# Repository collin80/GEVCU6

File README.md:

GEVCU
=====

Generalized Electric Vehicle Control Unit

Our website can be found at : http://www.evtv.me

A project to create a fairly Arduino compatible ECU firmware
to interface with various electric vehicle hardware over CANbus
(and possibly other comm channels)

The project now builds in the Arduino IDE. So, use it to compile, send the firmware to the GEVCU hardware, and monitor serial. It all works very nicely.

You will need the following to have any hope of compiling and running the firmware:
- A GEVCU board. This version supports hardware 6.23c and later.
- Arduino IDE 1.5.4 - or later even 1.8.13 or such newer IDEs should work fine.
-All libraries reside in the lib folder

All libraries belong in %USERPROFILE%\Documents\Arduino\libraries (Windows) or ~/Arduino/libraries (Linux/Mac).
You will need to remove -master or any other postfixes. Your library folders should be named as above.

The canbus is supposed to be terminated on both ends of the bus. If you are testing with a DMOC and GEVCU then you've got two devices, each on opposing ends of the bus. GEVCU hardware is already terminated internally.

This software is MIT licensed:

Copyright (c) 2014 Collin Kidder, Michael Neuweiler, Charles Galpin, Jack Rickard

Permission is hereby granted, free of charge, to any person obtaining
a copy of this software and associated documentation files (the
"Software"), to deal in the Software without restriction, including
without limitation the rights to use, copy, modify, merge, publish,
distribute, sublicense, and/or sell copies of the Software, and to
permit persons to whom the Software is furnished to do so, subject to
the following conditions:

The above copyright notice and this permission notice shall be included
in all copies or substantial portions of the Software.

THE SOFTWARE IS PROVIDED "AS IS", WITHOUT WARRANTY OF ANY KIND,
EXPRESS OR IMPLIED, INCLUDING BUT NOT LIMITED TO THE WARRANTIES OF
MERCHANTABILITY, FITNESS FOR A PARTICULAR PURPOSE AND NONINFRINGEMENT.
IN NO EVENT SHALL THE AUTHORS OR COPYRIGHT HOLDERS BE LIABLE FOR ANY
CLAIM, DAMAGES OR OTHER LIABILITY, WHETHER IN AN ACTION OF CONTRACT,
TORT OR OTHERWISE, ARISING FROM, OUT OF OR IN CONNECTION WITH THE
SOFTWARE OR THE USE OR OTHER DEALINGS IN THE SOFTWARE.

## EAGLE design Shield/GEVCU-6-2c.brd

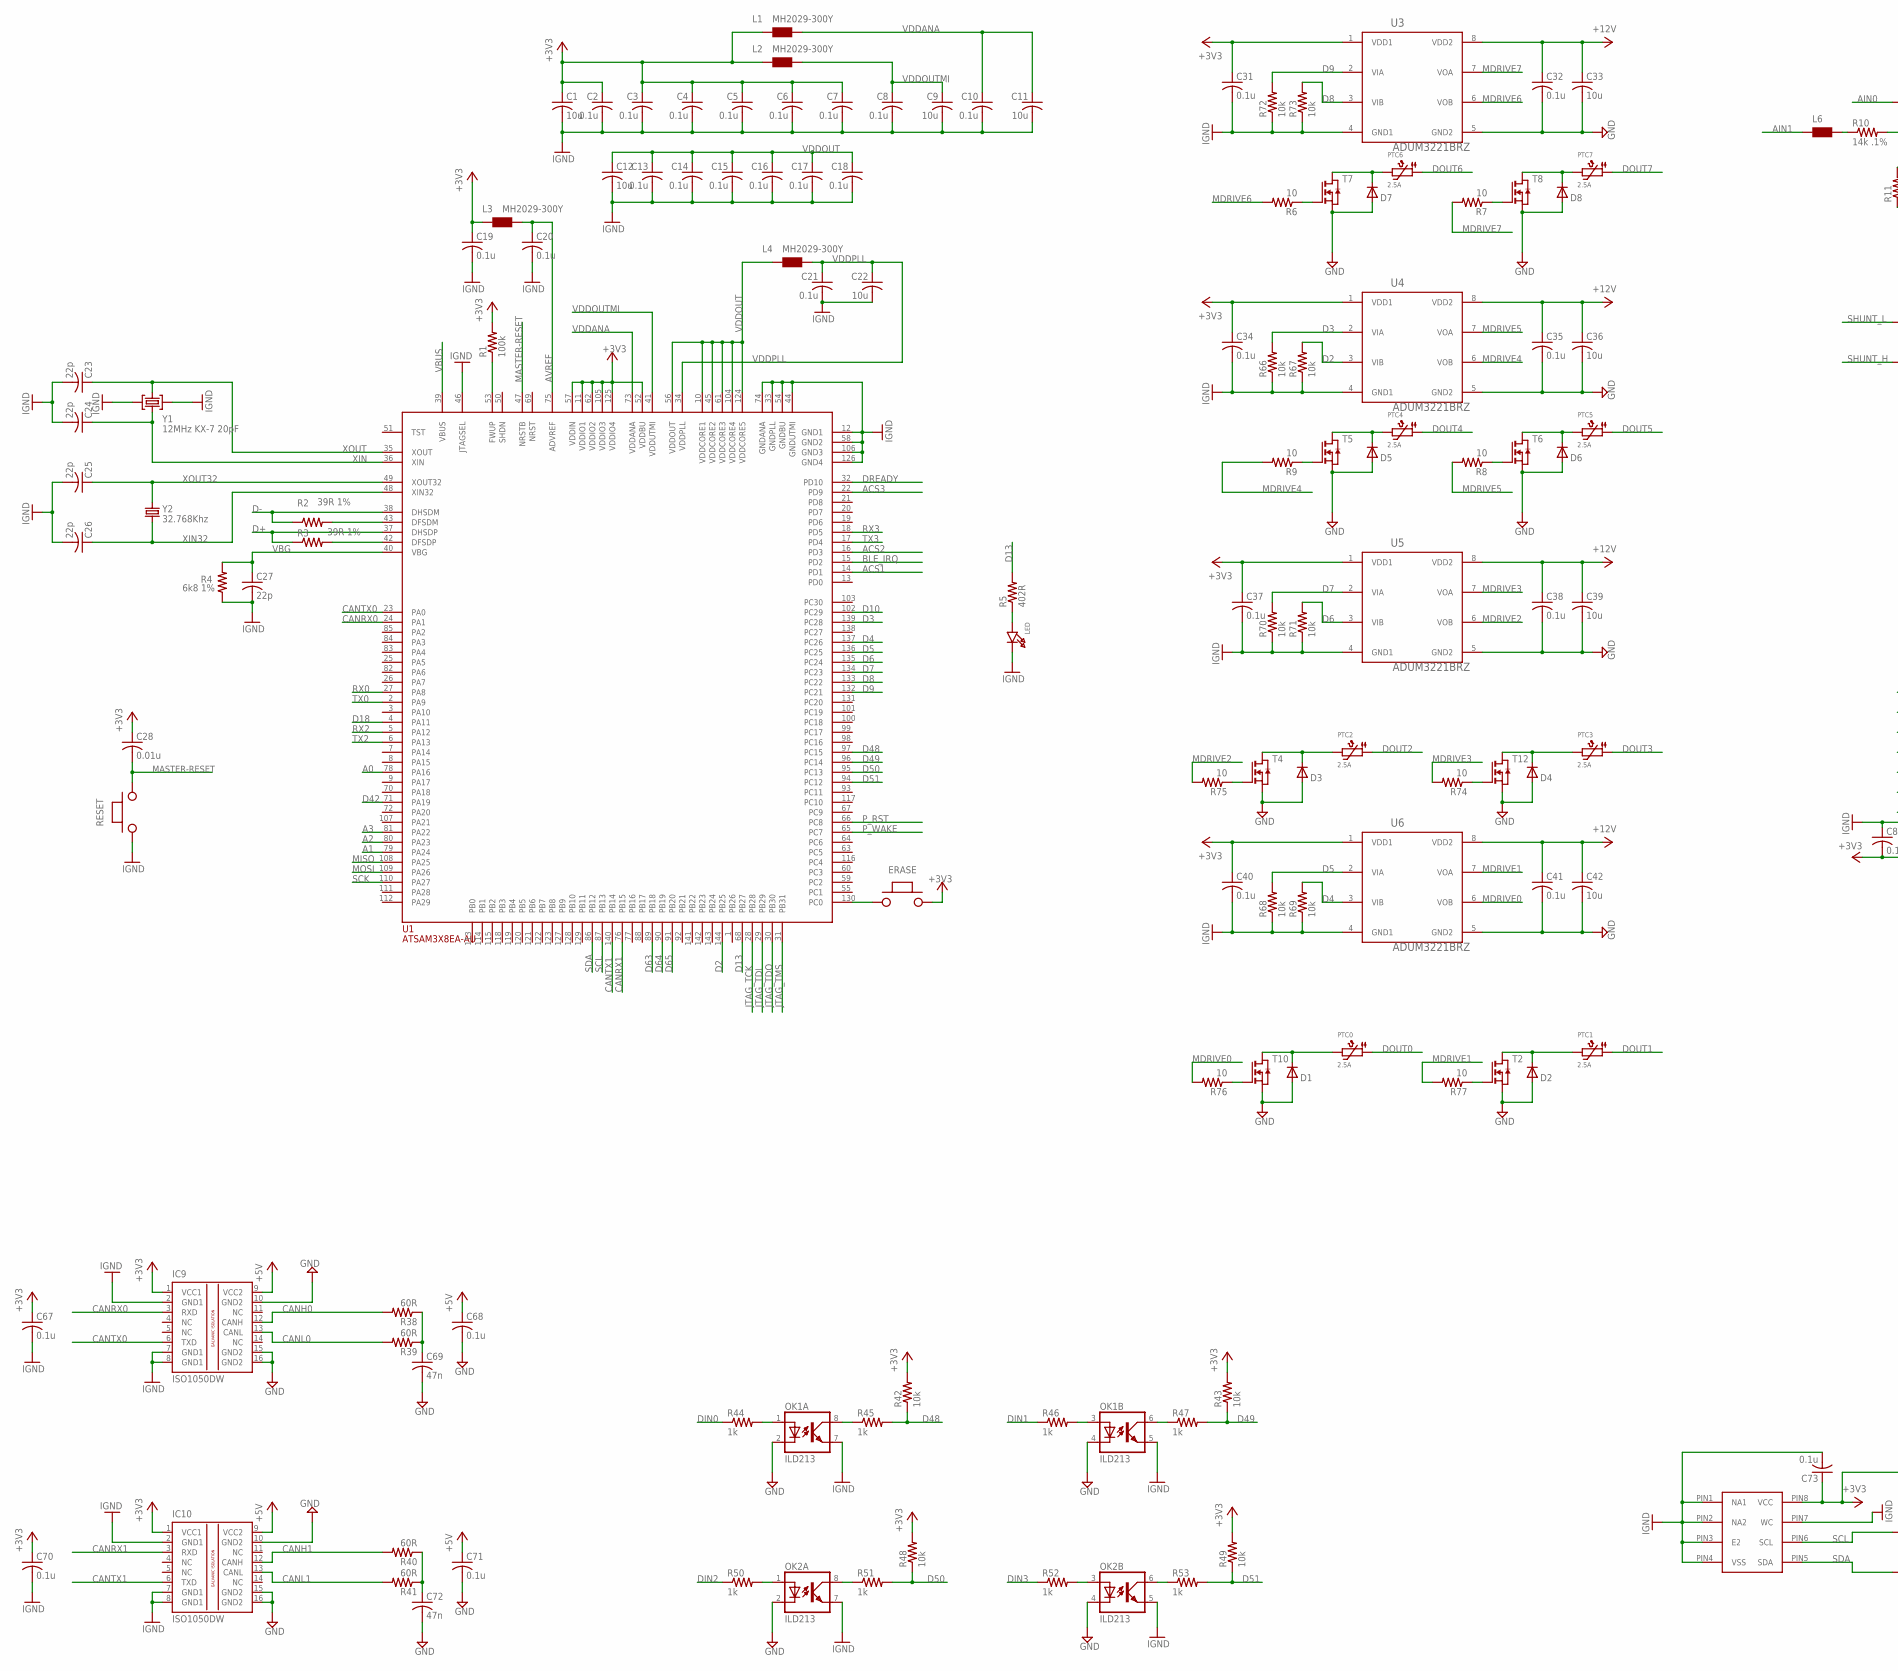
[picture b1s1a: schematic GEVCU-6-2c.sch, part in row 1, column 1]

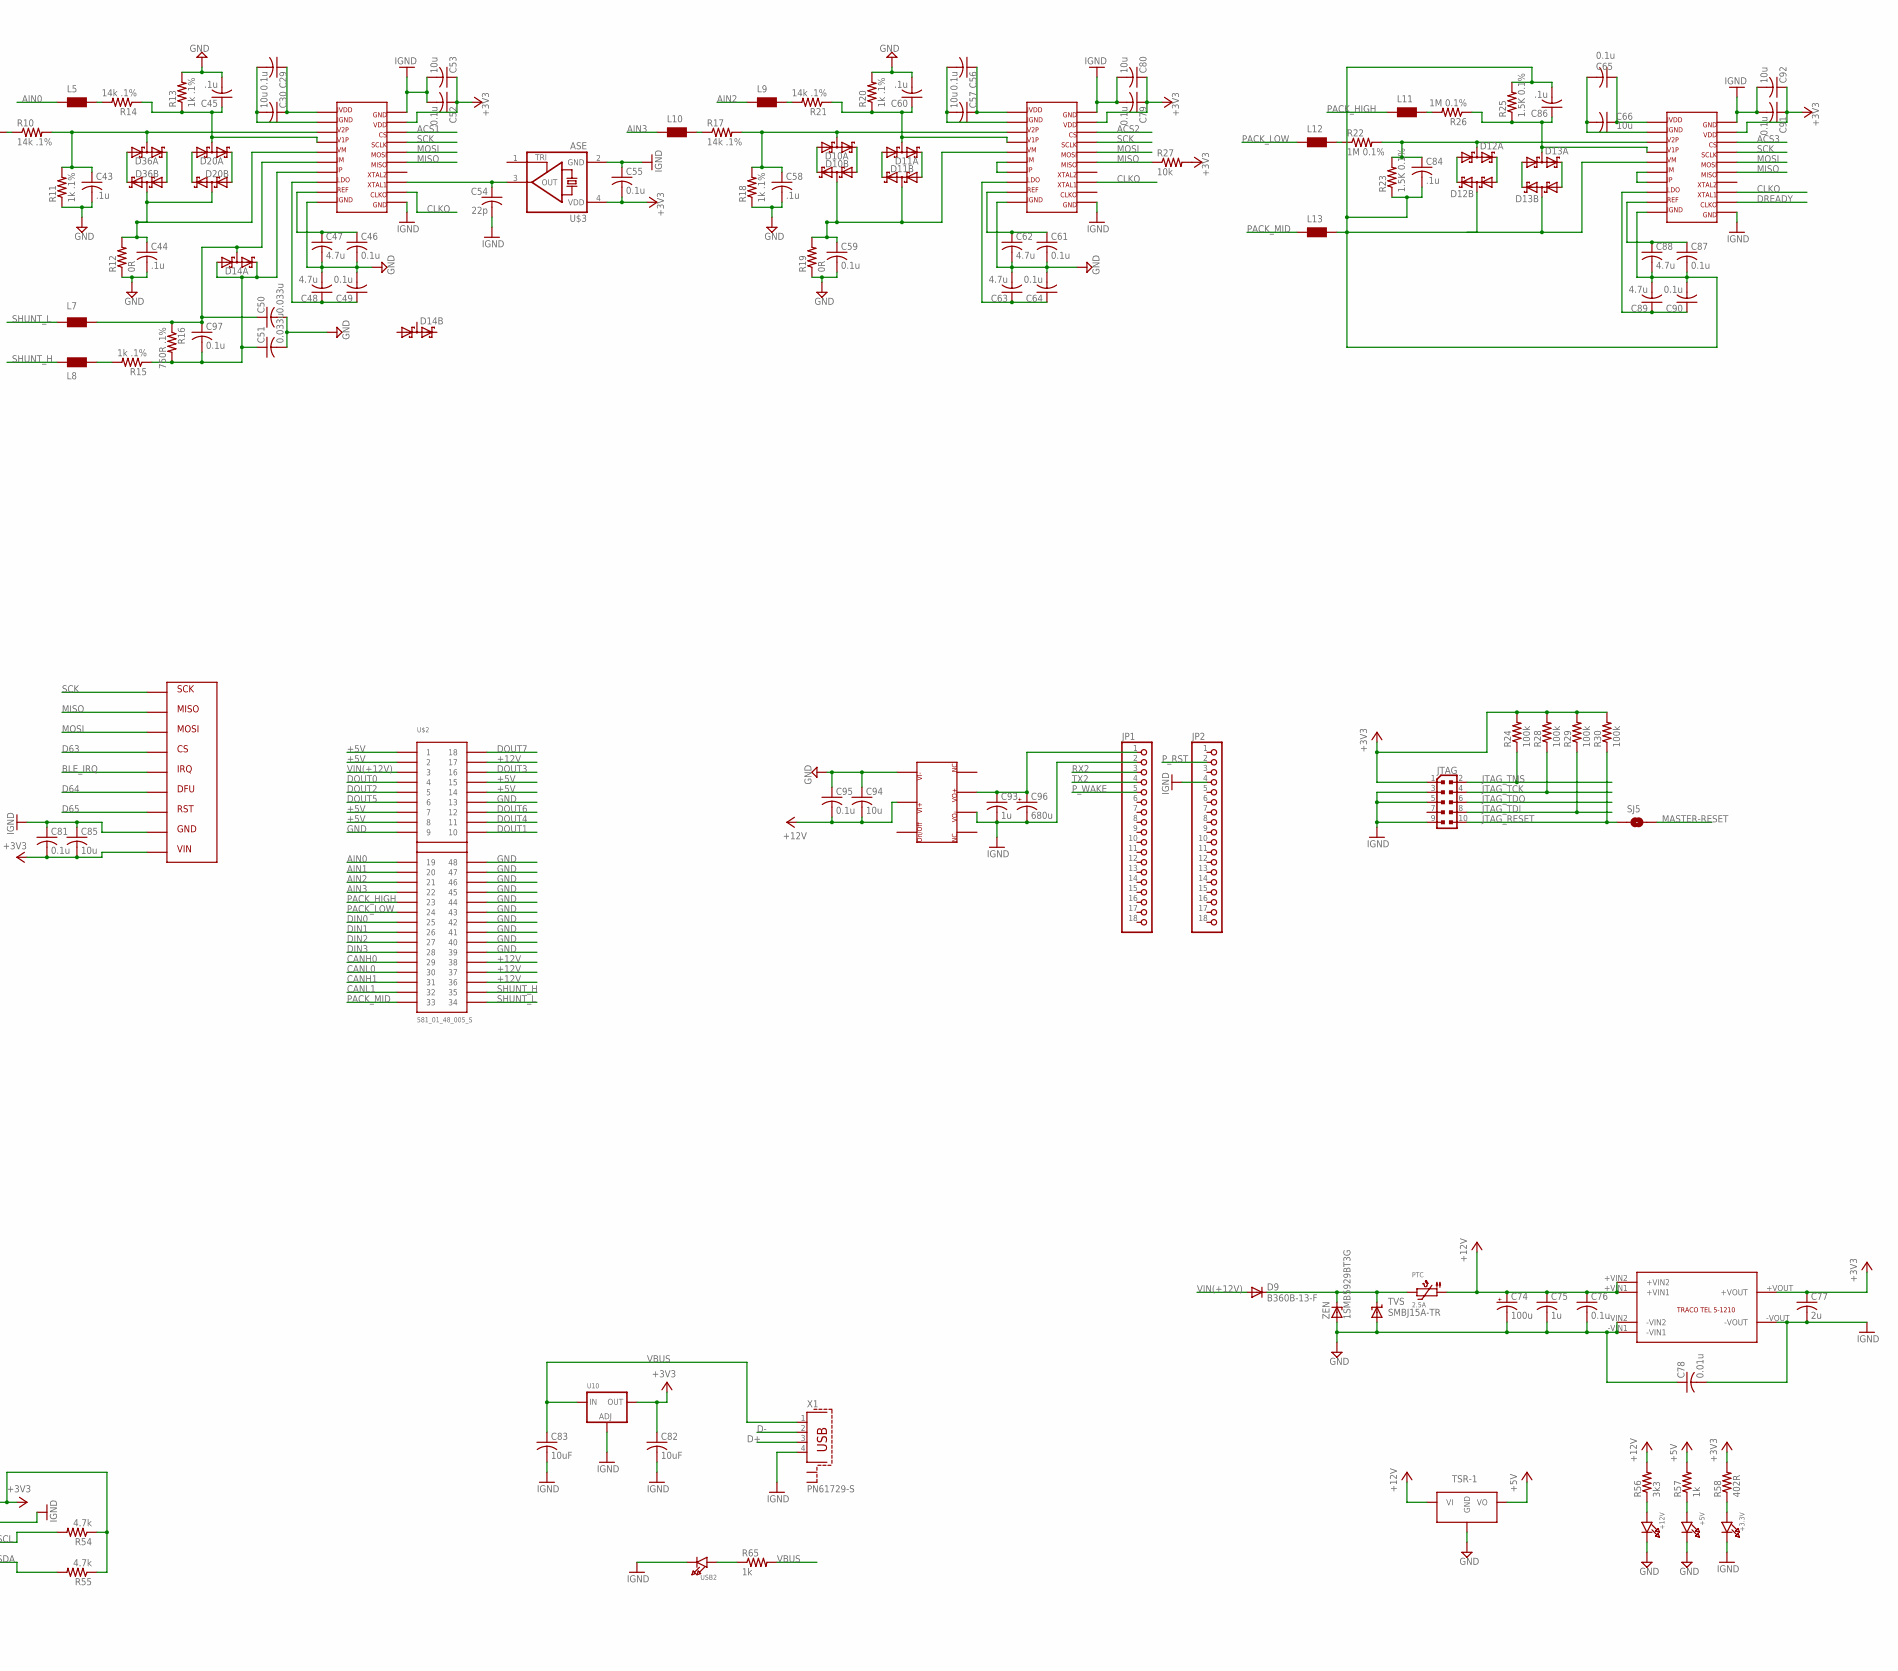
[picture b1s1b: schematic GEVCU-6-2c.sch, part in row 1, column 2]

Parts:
+3.3V, +5V, +12V: LED0805; CHIPLED_0805
C1, C9, C11, C12, C22, C30, C33, C36, C39, C42, C53, C57, C66, C80, C85, C92, C94: 10u; C0805
C2, C3, C4, C5, C6, C7, C8, C10, C13, C14, C15, C16, C17, C18, C19, C20, C21, C29, C31, C32, C34, C35, C37, C38, C40, C41, C46, C49, C52, C55, C56, C59, C61, C64, C65, C67, C68, C70, C71, C73, C76, C79, C81, C87, C90, C91, C95, C97: 0.1u; C0805
C23, C24, C54: 22p; C1206
C25, C26, C27: 22p; C0805
C28: 0.01u; C0805
C43, C44, C45, C58, C60, C84, C86: .1u; C0805
C47, C48, C62, C63, C88, C89: 4.7u; C0805
C50, C51: 0.033u; C0805
C69, C72: 47n; C0805
C74: 100u; E2,5-6
C75, C93: 1u; C0805
C77: 2u; C0805
C78: 0.01u; C1812
C82, C83: 10uF; C0805
C96: 680u; E5-10,5
D1, D2, D3, D4, D5, D6, D7, D8: MBR0520LT; SOD123
D9: B360B-13-F; SMB
D10, D11, D12, D13, D14, D20, D36: BAS70XY; SOT363_PHILIPS
ERASE: PUCHBUTTON
IC9, IC10: ISO1050DW; DUB-R-PDSO-G8
JP1, JP2: PINHD-1X18; 1X18
JTAG: PINHEAD_PINHD-2X5PASSO127; PINHEAD_2X05_127
L1, L2, L3, L4, L5, L6, L7, L8, L9, L10, L11, L12, L13: MH2029-300Y; 0805
LED: LED0805; CHIPLED_0805
OK1, OK2: ILD213; SOIC08
PTC, PTC0, PTC1, PTC2, PTC3, PTC4, PTC5, PTC6, PTC7: 2.5A; PTC1812
R1, R24, R28, R29, R30: 100k; R0805
R2, R3: 39R 1%; R0805
R4: 6k8 1%; R0805
R5, R58: 402R; R0805
R6, R7, R8, R9, R74, R75, R76, R77: 10; R0805
R10, R14, R17, R21: 14k .1%; R0805
R11, R13, R15, R18, R20: 1k .1%; R0805
R12, R19: 0R; R0805
R16: 750R .1%; R0805
R22, R26: 1M 0.1%; R1206
R23, R25: 1.5K 0.1%; R0805
R27, R42, R43, R48, R49, R66, R67, R68, R69, R70, R71, R72, R73: 10k; R0805
R38, R39, R40, R41: 60R; R0805
R44, R45, R46, R47, R50, R51, R52, R53, R57, R65: 1k; R0805
R54, R55: 4.7k; R0805
R56: 3k3; R0805
RESET: PUCHBUTTON
SJ5: SOLDERJUMPERNO; SJ_2S-NO
T2, T4, T5, T6, T7, T8, T10, T12: NMOSSOT223; SOT223
TVS: SMBJ15A-TR; SMBJ
U1: ATSAM3X8EA-AU; LQFP144
U3, U4, U5, U6: ADUM3221BRZ; SOIC127P600X175-8N
U7: CK_CUSTOM_M24M02-DRMN6TP; CK_CUSTOM_SOIC8
U8: TRACO
U9: TSR-1
U10: LM1117SOT223-WAVE; SOT223-W
U11, U12, U24: ADE7913; SOIC20
U$1: CINCON5V
U$2: 581_01_48_005_S
U$3: ASE
U$4: BLE_SPI
USB2: LED0805; CHIPLED_0805
X1: PN61729-S
Y1: 12MHz KX-7 20pF; CRYSTAL-3.2-2.5
Y2: 32.768Khz; ARDUINO_WIFI_SHIELD_V018_TG_RESONATOR_EPSON_FC_145
ZEN: 1SMB5929BT3G; SMB

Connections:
+3V3: C1.1, C2.1, C3.1, C4.1, C5.1, C6.1, C7.1, C19.1, C28.1, C31.1, C34.1, C37.1, C40.1, C52.1, C53.1, C55.2, C67.1, C70.1, C73.1, C77.1, C79.1, C80.1, C81.2, C82.1, C85.2, C91.1, C92.1, ERASE.P$2, IC9.1 (VCC1), IC10.1 (VCC1), JTAG.1, L1.1, L2.1, L3.1, R1.2, R24.2, R27.2, R28.2, R29.2, R30.2, R42.2, R43.2, R48.2, R49.2, R54.1, R55.1, R58.2, U1.11 (VDDIO1), U1.52 (VDDBU), U1.57 (VDDIN), U1.62 (VDDIO2), U1.105 (VDDIO3), U1.125 (VDDIO4), U3.1 (VDD1), U4.1 (VDD1), U5.1 (VDD1), U6.1 (VDD1), U7.PIN8 (VCC), U8.+VOUT, U10.2 (OUT), U11.19, U12.19, U24.19, U$3.4 (VDD), U$4.P$9
+5V: C68.1, C71.1, IC9.9 (VCC2), IC10.9 (VCC2), R57.2, U9.P$3 (VO), U$2.P$1 (1), U$2.P$2 (2), U$2.P$7 (7), U$2.P$8 (8), U$2.P$14 (14), U$2.P$15 (15)
+12V: C32.1, C33.1, C35.1, C36.1, C38.1, C39.1, C41.1, C42.1, C74.+, C75.1, C76.1, C94.2, C95.2, PTC.P$1 (1), R56.2, U3.8 (VDD2), U4.8 (VDD2), U5.8 (VDD2), U6.8 (VDD2), U8.+VIN1, U8.+VIN2, U9.P$1 (VI), U$1.P$2, U$2.P$17 (17), U$2.P$36 (36), U$2.P$37 (37), U$2.P$38 (38)
A0: U1.78 (PA16)
A1: U1.79 (PA24)
A2: U1.80 (PA23)
A3: U1.81 (PA22)
ACS1: U1.14 (PD1), U11.18
ACS2: U1.16 (PD3), U12.18
ACS3: U1.22 (PD9), U24.18
AIN0: L5.1, U$2.P$19 (19)
AIN1: L6.1, U$2.P$20 (20)
AIN2: L9.1, U$2.P$21 (21)
AIN3: L10.1, U$2.P$22 (22)
AVREF: C20.1, L3.2, U1.75 (ADVREF)
BLE_IRQ: U1.15 (PD2), U$4.P$5
CANH0: IC9.12 (CANH), R38.2, U$2.P$29 (29)
CANH1: IC10.12 (CANH), R40.2, U$2.P$31 (31)
CANL0: IC9.13 (CANL), R39.2, U$2.P$30 (30)
CANL1: IC10.13 (CANL), R41.2, U$2.P$32 (32)
CANRX0: IC9.3 (RXD), U1.24 (PA1)
CANRX1: IC10.3 (RXD), U1.76 (PB15)
CANTX0: IC9.6 (TXD), U1.23 (PA0)
CANTX1: IC10.6 (TXD), U1.140 (PB14)
CLKO: U11.12, U12.13, U24.13
D2: R67.2, U1.144 (PB25), U4.3 (VIB)
D3: R66.2, U1.139 (PC28), U4.2 (VIA)
D4: R69.2, U1.137 (PC26), U6.3 (VIB)
D5: R68.2, U1.136 (PC25), U6.2 (VIA)
D6: R71.2, U1.135 (PC24), U5.3 (VIB)
D7: R70.2, U1.134 (PC23), U5.2 (VIA)
D8: R73.2, U1.133 (PC22), U3.3 (VIB)
D9: R72.2, U1.132 (PC21), U3.2 (VIA)
D10: U1.102 (PC29)
D13: R5.2, U1.68 (PB27)
D18: U1.4 (PA11)
D42: U1.71 (PA19)
D48: R42.1, R45.2, U1.97 (PC15)
D49: R43.1, R47.2, U1.96 (PC14)
D50: R48.1, R51.2, U1.95 (PC13)
D51: R49.1, R53.2, U1.94 (PC12)
D63: U1.89 (PB18), U$4.P$4
D64: U1.90 (PB19), U$4.P$6
D65: U1.91 (PB20), U$4.P$7
D+: R3.1, U1.37 (DHSDP), X1.3
D-: R2.1, U1.38 (DHSDM), X1.2
DIN0: R44.1, U$2.P$25 (25)
DIN1: R46.1, U$2.P$26 (26)
DIN2: R50.1, U$2.P$27 (27)
DIN3: R52.1, U$2.P$28 (28)
DOUT0: PTC0.P$1 (1), U$2.P$4 (4)
DOUT1: PTC1.P$1 (1), U$2.P$10 (10)
DOUT2: PTC2.P$1 (1), U$2.P$5 (5)
DOUT3: PTC3.P$1 (1), U$2.P$16 (16)
DOUT4: PTC4.P$1 (1), U$2.P$11 (11)
DOUT5: PTC5.P$1 (1), U$2.P$6 (6)
DOUT6: PTC6.P$1 (1), U$2.P$12 (12)
DOUT7: PTC7.P$1 (1), U$2.P$18 (18)
DREADY: U1.32 (PD10), U24.12
ERASE_S: ERASE.P$1, U1.130 (PC0)
GND: +5V.C, +12V.C, C32.2, C33.2, C35.2, C36.2, C38.2, C39.2, C41.2, C42.2, C43.2, C44.2, C45.2, C46.2, C47.2, C48.2, C49.2, C50.2, C51.2, C58.2, C59.2, C60.2, C61.2, C62.2, C63.2, C64.2, C68.2, C69.2, C71.2, C72.2, C74.-, C75.2, C76.2, C78.1, C94.1, C95.1, D1.A, D2.A, D3.A, D4.A, D5.A, D6.A, D7.A, D8.A, IC9.10 (GND2), IC9.15 (GND2), IC9.16 (GND2), IC10.10 (GND2), IC10.15 (GND2), IC10.16 (GND2), OK1.2 (C), OK1.4 (C), OK2.2 (C), OK2.4 (C), R11.1, R12.1, R13.2, R18.1, R19.1, R20.2, T2.3 (S), T4.3 (S), T5.3 (S), T6.3 (S), T7.3 (S), T8.3 (S), T10.3 (S), T12.3 (S), TVS.A, U3.5 (GND2), U4.5 (GND2), U5.5 (GND2), U6.5 (GND2), U8.-VIN1, U8.-VIN2, U9.P$2 (GND), U11.10, U12.10, U$1.P$1, U$2.P$9 (9), U$2.P$13 (13), U$2.P$39 (39), U$2.P$40 (40), U$2.P$41 (41), U$2.P$42 (42), U$2.P$43 (43), U$2.P$44 (44), U$2.P$45 (45), U$2.P$46 (46), U$2.P$47 (47), U$2.P$48 (48), ZEN.A
IGND: +3.3V.C, C1.2, C2.2, C3.2, C4.2, C5.2, C6.2, C7.2, C8.2, C9.2, C10.2, C11.2, C12.2, C13.2, C14.2, C15.2, C16.2, C17.2, C18.2, C19.2, C20.2, C21.2, C22.2, C23.2, C24.2, C25.2, C26.2, C27.2, C31.2, C34.2, C37.2, C40.2, C52.2, C53.2, C54.2, C55.1, C67.2, C70.2, C73.2, C77.2, C78.2, C79.2, C80.2, C81.1, C82.2, C83.2, C85.1, C91.2, C92.2, C93.2, C96.-, IC9.2 (GND1), IC9.7 (GND1), IC9.8 (GND1), IC10.2 (GND1), IC10.7 (GND1), IC10.8 (GND1), JP1.2, JP2.4, JTAG.3, JTAG.5, JTAG.9, LED.C, OK1.5 (EMIT), OK1.7 (EMIT), OK2.5 (EMIT), OK2.7 (EMIT), R4.1, R66.1, R67.1, R68.1, R69.1, R70.1, R71.1, R72.1, R73.1, RESET.P$1, U1.12 (GND1), U1.33 (GNDPLL), U1.44 (GNDUTMI), U1.46 (JTAGSEL), U1.54 (GNDBU), U1.58 (GND2), U1.74 (GNDANA), U1.106 (GND3), U1.126 (GND4), U3.4 (GND1), U4.4 (GND1), U5.4 (GND1), U6.4 (GND1), U7.PIN1 (NA1), U7.PIN2 (NA2), U7.PIN3 (E2), U7.PIN4 (VSS), U7.PIN7 (WC), U8.-VOUT, U10.1 (ADJ), U11.11, U11.20, U12.11, U12.20, U24.11, U24.20, U$1.P$6, U$3.2 (GND), U$4.P$8, USB2.C, X1.4, Y1.2 (GND), Y1.4 (GND)
JTAG_RESET: JTAG.10, R30.1, SJ5.1
JTAG_TCK: JTAG.4, R28.1, U1.28 (PB28)
JTAG_TDI: JTAG.8, R29.1, U1.29 (PB29)
JTAG_TDO: JTAG.6, U1.30 (PB30)
JTAG_TMS: JTAG.2, R24.1, U1.31 (PB31)
MASTER-RESET: C28.2, RESET.P$2, SJ5.2, U1.47 (NRSTB)
MDRIVE0: R76.2, U6.6 (VOB)
MDRIVE1: R77.2, U6.7 (VOA)
MDRIVE2: R75.2, U5.6 (VOB)
MDRIVE3: R74.2, U5.7 (VOA)
MDRIVE4: R9.2, U4.6 (VOB)
MDRIVE5: R8.2, U4.7 (VOA)
MDRIVE6: R6.2, U3.6 (VOB)
MDRIVE7: R7.2, U3.7 (VOA)
MISO: R27.1, U1.108 (PA25), U11.15, U12.15, U24.15, U$4.P$2
MOSI: U1.109 (PA26), U11.16, U12.16, U24.16, U$4.P$3
unnamed: D36.1 (A1), D36.5 (C2)
unnamed: +3.3V.A, R58.1
unnamed: D9.C, PTC.P$2 (2), TVS.C, ZEN.C
unnamed: +5V.A, R57.1
unnamed: C29.1, C30.1, U11.1
unnamed: LED.A, R5.1
unnamed: L8.1, R15.2
unnamed: D36.2 (C2), D36.4 (A1)
unnamed: C45.1, D20.6 (C1A2), R13.1, R14.1, U11.4
unnamed: C29.2, C30.2, U11.2
unnamed: C43.1, D36.6 (C1A2), R10.2, R11.2, U11.3
unnamed: L5.2, R14.2
unnamed: C44.1, D20.3 (C1A2), D36.3 (C1A2), R12.2, U11.5
unnamed: C65.1, C66.1, U24.1
unnamed: C46.1, C47.1, U11.9
unnamed: C48.1, C49.1, U11.8
unnamed: L6.2, R10.1
unnamed: D20.1 (A1), D20.5 (C2)
unnamed: D20.2 (C2), D20.4 (A1)
unnamed: C51.1, C97.2, D14.1 (A1), D14.2 (C2), R15.1, R16.2, U11.7
unnamed: C50.1, C97.1, D14.6 (C1A2), L7.1, R16.1, U11.6
unnamed: C56.1, C57.1, U12.1
unnamed: C69.1, R38.1, R39.1
unnamed: C72.1, R40.1, R41.1
unnamed: OK1.1 (A), R44.2
unnamed: OK1.3 (A), R46.2
unnamed: OK1.8 (COL), R45.1
unnamed: OK1.6 (COL), R47.1
unnamed: C56.2, C57.2, U12.2
unnamed: OK2.6 (COL), R53.1
unnamed: D10.1 (A1), D10.5 (C2)
unnamed: OK2.8 (COL), R51.1
unnamed: C65.2, C66.2, U24.2
unnamed: OK2.1 (A), R50.2
unnamed: C54.1, U11.13, U$3.3 (OUT)
unnamed: OK2.3 (A), R52.2
unnamed: +12V.A, R56.1
unnamed: D10.2 (C2), D10.4 (A1)
unnamed: D2.C, PTC1.P$2 (2), T2.2 (D), T2.4 (D)
unnamed: C58.1, D10.6 (C1A2), R17.2, R18.2, U12.3
unnamed: D11.1 (A1), D11.5 (C2)
unnamed: D3.C, PTC2.P$2 (2), T4.2 (D), T4.4 (D)
unnamed: D11.2 (C2), D11.4 (A1)
unnamed: R2.2, U1.43 (DFSDM)
unnamed: C59.1, D10.3 (C1A2), D11.3 (C1A2), R19.2, U12.5
unnamed: C60.1, D11.6 (C1A2), R20.1, R21.1, U12.4
unnamed: R3.2, U1.42 (DFSDP)
unnamed: D5.C, PTC4.P$2 (2), T5.2 (D), T5.4 (D)
unnamed: D6.C, PTC5.P$2 (2), T6.2 (D), T6.4 (D)
unnamed: R1.1, U1.53 (FWUP)
unnamed: D7.C, PTC6.P$2 (2), T7.2 (D), T7.4 (D)
unnamed: D8.C, PTC7.P$2 (2), T8.2 (D), T8.4 (D)
unnamed: D4.C, PTC3.P$2 (2), T12.2 (D), T12.4 (D)
unnamed: D1.C, PTC0.P$2 (2), T10.2 (D), T10.4 (D)
unnamed: D12.1 (A1), D12.5 (C2)
unnamed: C61.1, C62.1, U12.9
unnamed: R65.1, USB2.A
unnamed: R6.1, T7.1 (G)
unnamed: R76.1, T10.1 (G)
unnamed: R77.1, T2.1 (G)
unnamed: R74.1, T12.1 (G)
unnamed: R75.1, T4.1 (G)
unnamed: R9.1, T5.1 (G)
unnamed: R8.1, T6.1 (G)
unnamed: R7.1, T8.1 (G)
unnamed: C63.1, C64.1, U12.8
unnamed: L9.2, R21.2
unnamed: L10.2, R17.1
unnamed: U12.6, U12.7
unnamed: D12.2 (C2), D12.4 (A1)
unnamed: C84.1, D12.6 (C1A2), R22.2, R23.2, U24.3
unnamed: D13.1 (A1), D13.5 (C2)
unnamed: D13.2 (C2), D13.4 (A1)
unnamed: D13.3 (C1A2), U24.5
unnamed: C86.1, D13.6 (C1A2), R25.1, R26.1, U24.4
unnamed: C87.1, C88.1, U24.9
unnamed: C89.1, C90.1, U24.8
unnamed: L11.2, R26.2
unnamed: L12.2, R22.1
unnamed: U24.6, U24.7
unnamed: C93.1, C96.+, JP1.1, U$1.P$5
unnamed: C84.2, C86.2, C87.2, C88.2, C89.2, C90.2, D12.3 (C1A2), L13.2, R23.1, R25.2, U24.10
PACK_HIGH: L11.1, U$2.P$23 (23)
PACK_LOW: L12.1, U$2.P$24 (24)
PACK_MID: L13.1, U$2.P$33 (33)
P_RST: JP2.2, U1.66 (PC8)
P_WAKE: JP1.5, U1.65 (PC7)
RX0: U1.27 (PA8)
RX2: JP1.3, U1.5 (PA12)
RX3: U1.18 (PD5)
SCK: U1.110 (PA27), U11.17, U12.17, U24.17, U$4.P$1
SCL: R54.2, U1.87 (PB13), U7.PIN6 (SCL)
SDA: R55.2, U1.86 (PB12), U7.PIN5 (SDA)
SHUNT_H: L8.2, U$2.P$35 (35)
SHUNT_L: L7.2, U$2.P$34 (34)
TX0: U1.2 (PA9)
TX2: JP1.4, U1.6 (PA13)
TX3: U1.17 (PD4)
VBG: C27.1, R4.2, U1.40 (VBG)
VBUS: C83.1, R65.2, U1.39 (VBUS), U10.3 (IN), X1.1
VDDANA: C10.1, C11.1, L1.2, U1.73 (VDDANA)
VDDOUT: C12.1, C13.1, C14.1, C15.1, C16.1, C17.1, C18.1, L4.1, U1.10 (VDDCORE1), U1.45 (VDDCORE2), U1.56 (VDDOUT), U1.61 (VDDCORE3), U1.104 (VDDCORE4), U1.124 (VDDCORE5)
VDDOUTMI: C8.1, C9.1, L2.2, U1.41 (VDDUTMI)
VDDPLL: C21.1, C22.1, L4.2, U1.34 (VDDPLL)
VIN(+12V): D9.A, U$2.P$3 (3)
XIN: C24.1, U1.36 (XIN), Y1.1 (C1)
XIN32: C26.1, U1.48 (XIN32), Y2.P$2 (2)
XOUT: C23.1, U1.35 (XOUT), Y1.3 (C2)
XOUT32: C25.1, U1.49 (XOUT32), Y2.P$1 (1)

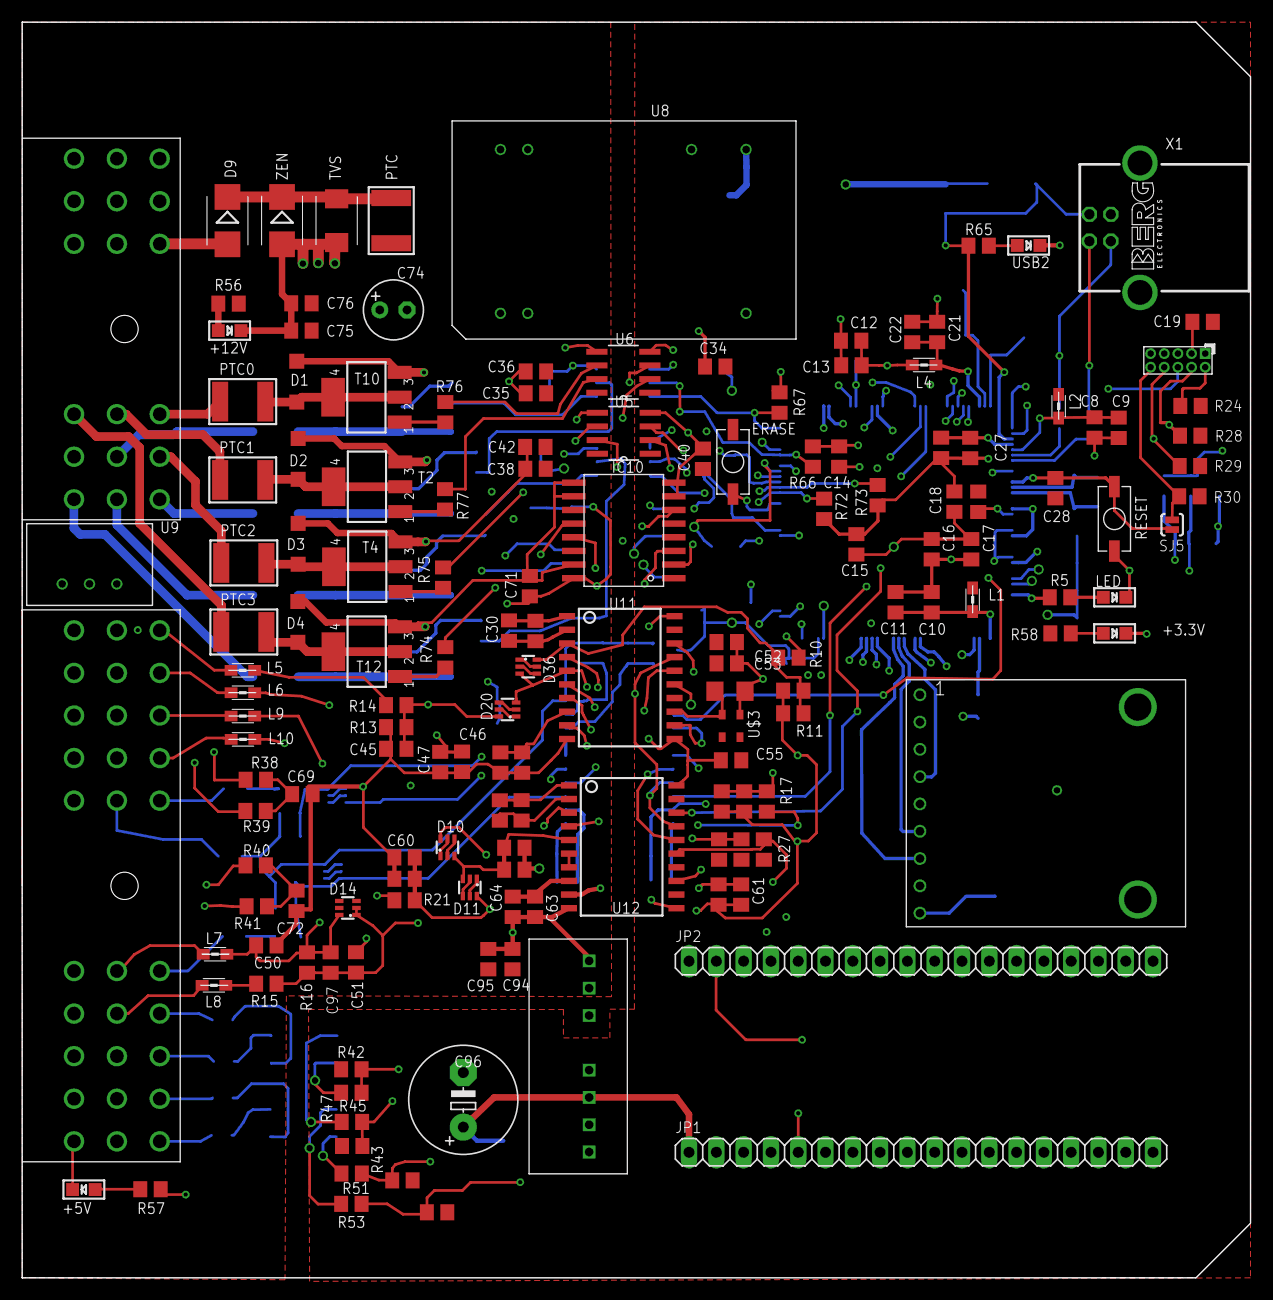
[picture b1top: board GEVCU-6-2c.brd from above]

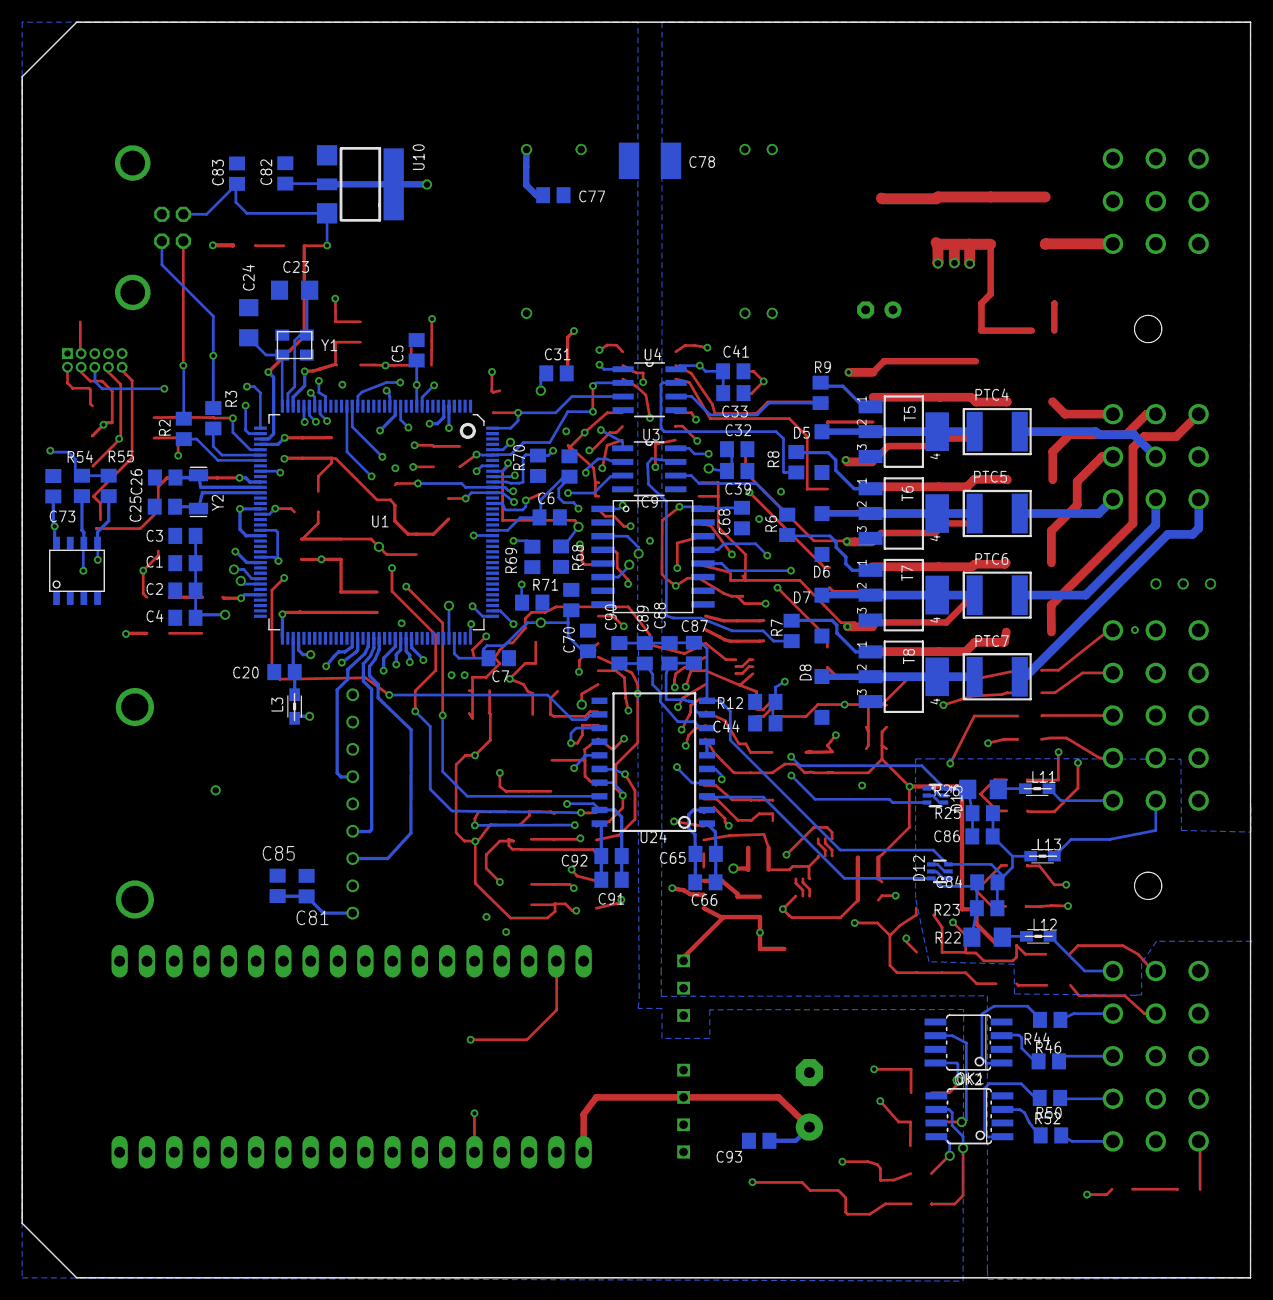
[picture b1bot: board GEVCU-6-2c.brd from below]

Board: 4 copper layers, 114.3 x 116.8 mm, 243 parts (90 on the bottom side), 176 nets.

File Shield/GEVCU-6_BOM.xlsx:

Qty | Value | Device | Part Number | Vendor | Parts | Picture
5 | GREEN | LED0805 | 645-598-8170-107F | Mouser | +3.3V, +5V, +12V, LED, USB2
19 | 10u | C-USC0805 | 80-C0805C106K8P | Mouser | C1, C9, C11, C12, C22, C30, C33, C36, C39, C42, C53, C57, C66, C80, C82, C83, C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
46 | 0.1u | C-USC0805 | 80-C0805C104J8R | Mouser | C2, C3, C4, C5, C6, C7, C8, C10, C13, C14, C15, C16, C17, C18, C19, C20, C21, C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
3 | 22p | C-USC1206 | 77-VJ1206A220JXQCBC | Mouser | C23, C24, C54
3 | 22p | C-USC0805 | 581-0805ZA220JAT2A | Mouser | C25, C26, C27
1 | 0.01u | C-USC0805 | 77-VJ0805A103KXQTBC | Mouser | C28
10 | 0.033u | C-USC0805 | 77-VJ0805Y333KBABC31 | Mouser | C43, C44, C45, C50, C51, C58, C59, C60, C84, C86
6 | 4.7u | C-USC0805 | 810-CGA4J1X7R1E475MA | Mouser | C47, C48, C62, C63, C88, C89
2 | 47n | C-USC0805 | 581-0805ZC473JAZ2A | Mouser | C69, C72
1 | 100u | CPOL-USE2.5-6 | 667-EEU-FM1E101 | Mouser | C74
2 | 1u | C-USC0805 | 80-C0805C105J3RACTU | Mouser | C75, C93
1 | 2u | C-USC0805 | 810-CGA4J1X7R1V225K | Mouser | C77
1 | 0.01u 2kv | C-USC1812 | 605-202S43W103KV4E | Mouser | C78
1 | 680u | CPOL-US5-10.5 | 661-EKZM250E681MJ16S | Mouser | C96
8 | MBR0520LT | MBR0520LT | 512-MBR0520L | Mouser | D1, D2, D3, D4, D5, D6, D7, D8
1 | B360B-13-F | DIODE-SMB | 621-B360B-F | Mouser | D9
7 | BAS70XY | BAS70XY | 771-BAS70XY115 | Mouser | D10, D11, D12, D13, D14, D20, D36
2 | PUCHBUTTON | PUSHBUTTON | 688-SKQYAB | Mouser | ERASE, RESET
2 | ISO1050DW | ISO1050 | 595-ISO1050DW | Mouser | IC9, IC10
2 | 1x18HEADER | PINHD_1x18 | 517-929850-01-18-RA | Mouser | JP1, JP2
13 | MH2029-300Y | WE-CBF_0805 | 652-MH2029-300Y | Mouser | L1, L2, L3, L4, L5, L6, L7, L8, L9, L10, L11, L12, L13
2 | ILD213 | ILD213 | 782-ILD213T | Mouser | OK1, OK2
9 | 2.5A | PTC1812 | 576-1812L150/12DR | Mouser | PTC, PTC0, PTC1, PTC2, PTC3, PTC4, PTC5, PTC6, PTC7
5 | 100k | R-US_R0805 | 71-CRCW0805J-100K-E3 | Mouser | R1, R24, R28, R29, R30
2 | 39R 1% | R-US_R0805 | 71-CRCW0805-39 | Mouser | R2, R3
1 | 6k8 1% | R-US_R0805 | 71-CRCW0805-6.8K-E3 | Mouser | R4
2 | 402R | R-US_R0805 | 71-CRCW0805-402-E3 | Mouser | R5, R58
8 | 10R | R-US_R0805 | 667-ERJ-6GEYJ100V | Mouser | R6, R7, R8, R9, R74, R75, R76, R77
17 | 10k | R-US_R0805 | 667-ERJ-6GEYJ103V | Mouser | R10, R14, R17, R21, R27, R42, R43, R48, R49, R66, R67, R68, R69, R70, R71, R72,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
18 | 1k | R-US_R0805 | 71-RCG08051K00JNEA | Mouser | R11, R12, R13, R15, R16, R18, R19, R20, R44, R45, R46, R47, R50, R51, R52, R53,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
2 | 1M | R-US_R1206 | 71-TNPV12061M00BEEN | Mouser | R22, R26
2 | 2K | R-US_R0805 | 279-RP73PF2A2K0BTDF | Mouser | R23, R25
4 | 60R | R-US_R0805 | 667-ERJ-P06D60R4V | Mouser | R38, R39, R40, R41
2 | 4.7k | R-US_R0805 | 71-CRCW0805J-4.7K-E3 | Mouser | R54, R55
1 | 3k3 | R-US_R0805 | 660-RK73G2ATTD3301F | Mouser | R56
8 | NMOSSOT223 | NMOSSOT223 | 726-BSP295H6327XTSA1 | Mouser | T2, T4, T5, T6, T7, T8, T10, T12
1 | SMBJ15A-TR | SUPPRESSOR_SMB | 511-SMBJ15A | Mouser | TVS
1 | CINCON5V | Tracor | TMR 6-2411WI | Mouser | U$1
1 | 581_01_48_005_S | 581_01_48_005_S | 581-01-48-005 | Mouser | U$2
1 | ASE | ASE | 788-8103AI233E-4.0X | Mouser | U$3
1 | ATSAM3X8EA-AU | ATSAM3X | 556-ATSAM3X8EA-AU | Mouser | U1
4 | ADUM3221BRZ | ADUM3221 | 584-ADUM3221BRZ | Mouser | U3, U4, U5, U6
1 | M24M02-DRMN6TP | EEPROM | 511-M24M02-DRMN6TP | Mouser | U7
1 | TRACO | TRACO | TEL5-1210 | Powergate | U8
1 | TSR-1 | TSR-1 | TSR1-2450 | Powergate | U9
1 | LM1117 | LM1117 | 926-LM1117IMPX33NOPB | Mouser | U10
3 | ADE7913 | ADE7913 | 584-ADE7913ARIZ | Mouser | U11, U12, U24
1 | PN61729-S | PN61729 | 292304-1 | Mouser | X1
1 | 12MHz | CRYSTAL-3.2x2.5 | 520-120-20-33-CKMT | Mouser | Y1
1 | 32.768Khz | 32.768Khz | 732-FC135-32.76KAAC3 | Mouser | Y1
1 | 1SMB5929BT3G | ZENER-DIODESMB | 863-1SMB5929BT3G | Mouser | ZEN
1 | 2x10 Header | 2x10 1.27mm Header | 855-M50-3500542 | Mouser | JTAG
Parts not placed onto PCB:
48 | 18ga pins for cinch plug |  | 538-425-00-00-873 | Mouser |  |  |  | 0.9
1 | 30 pin plug for 48 pin enclosure |  | 538-581-01-30-029 | Mouser |  |  |  | 59
1 | 18 pin plug for 48 pin enclosure |  | 538-581-01-18-023 | Mouser |  |  |  | 55
1 | MODICE Enclosure |  | 538-581-01-30-043 | Mouser |  |  |  | 98

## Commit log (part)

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2016-07-01 Add support for GEVCU 6.2 boards with the new 24 bit ADC. Add ability to set offset and gain for all analog inputs
2016-07-01 Keep log level at 1 on start up
2016-07-01 Disable fault handler again (still broken and slow), add routine to automatically determine proper ADC offsets
2016-07-07 Restylized all source files to be harmonized.
2016-07-12 Add support for custom motor controller board driving DMOC645 power section, add firmware receiver but commented out for now, updated version number, add GEVCU6.2 board files and BOM
2016-07-18 Fixes on GEVCU board files, addition of an Eagle library that contains some of the parts on the GEVCU board.
2016-07-19 Update GEVCU6 BOM, add parts list for GEVCU6, remove some ancient boards
2016-07-19 Initial pass at adding support for AdaFruit BLE. Most config is done but no parameter updating actually happens yet.
2016-07-20 Additional implementation of BLE code - added presentation bytes for all characteristics, added more characteristics.
2016-07-22 Switched to sending structs instead of individual values since BLE module can only handle 30 characteristics. Got things working for sending out parameters but often the updating command fails. Don't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
2016-07-27 Added detailed specification for 40 pin main connector from main CPU board to power board in the DMOC645.
2016-07-29 Fixes for data alignment problems.
2016-07-31 Added a few more data items to BLE data comm. Added state of charge to BatteryManager - no idea why it wasn't already there.
2016-08-02 Added a test throttle and test inverter that can be used to test the new BLE system without actual hardware or can be used for testing. Fixed up some BLE bugs.
2016-08-03 Fixed timeRunning, sped up and reorganized characteristic updates
2016-09-01 Added ability to retrieve changed BLE characteristics and use them to update the system
2016-09-02 Switch system I/O functionality to a class instead of bare C++ functions. Add ability to register CAN connected I/O into the system.
2016-09-02 Added more advanced CAN handler from ArduinoDue / Private branch. Now can do CANOpen as well. Added PowerKeyPro device driver.
2016-09-19 Fixes for CANIO, fixes and clean up for system EEPROM settings, addition of a module to use for vehicle specific code
2016-09-19 Changes to allow CK Inverter to work with gear and enable status set by rest of code (instead of being hardcoded)
2016-09-19 Switch to only initialize BLE module at first power up and then use the existing configuration from then on.
2016-09-21 Fix to initialization, fix for crash with parameter setting, status updates
2016-09-21 Disable GATT checking for updates. It's broken and does bad things.
2016-09-21 Fix automatic ADC compensation
2016-09-21 Add ability to dump device table or reinitialize it. Both for debugging.
2016-09-21 Change text output of device table init to be console instead of debug
2016-09-22 Switched up code to support negative ADC readings (only for GEVCU6). That board has full support for negative readings as well. Switched GEVCU6 ADC to be 13 bit signed which essentially gives it the 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
2016-09-23 Change device table dump to use console instead of info logging level
2016-09-23 Set log level to be 3 by default
2016-09-23 Remove iChip code which is not applicable to GEVCU6
2016-09-23 Remove system IO functionality not needed for GEVCU6
2016-09-23 Serial Console Cleanup
    Tried to rationalize our menu system in Serial Console. I failed. But
    artfully I hope.
2016-09-24 Read me updates
    Updated read me. We can now use Arduino IDE’s later than 1.54.
    Termination is built into the new hardware. The GEVCU6 version only
    supports new 6.23c or later hardware.
2016-09-25 Updated version number, fixed Vehicle Specific so it can be turned on/off now, added missing feedback messages in serial console
2016-09-26 Code change to hopefully alleviate device table resets, zero out parameters over BLE that don't get used.
2016-09-30 Switched from polled mode to callbacks for GATT characteristic changes
2016-10-02 Switch to using a polled state machine for analog setup (shrinks start up time). Also disabled more of fault handler also to save start up time.
2016-10-02 Fixed speed mode on DMOC, sped up I2C comm quite a bit, testing for interrupts with BLE
2016-10-05 Mostly just cosmetic changes to code lines
2016-10-05 Added extra debugging to DMOC code, caused DMOC to not regen unless there is some RPM
2016-10-08 200 rpm torque command modification
    Commented out cancellation of regen for rpm < 200. This is actually
    quite dangerous.
    If brake input is used for regen, you get strong regenerative braking
    for a given pedal input. But as rpm decreases below 200, the regen is
    suddenly released and the car surges forward suddenly - just as you
    slow down to stop before a car in front of you at a stoplight.
2016-10-10 Throttle fixes (allow negatives since this board can generate them), taper regen on DMOC as speed lowers, source code restructuring
2016-10-10 Small fix to clean up extraneous info messages when throttle is weird
2016-10-13 Fixes to make device initialization safer, addition of ability to automatically set up to 6 devices active when initializing for the first time
2016-10-17 DEBUGGING BUILD. DON'T USE THIS COMMIT FOR ANYTHING YOU CARE ABOUT. With that out of the way, beginnings of functional BLE code that can re-initialize the module and send updated parameters without u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
2016-10-21 Added some preliminaries for more BLE work, tightened up SPI transaction in sys_io
2016-10-21 Addition of hardware watchdog enable, better bounds checking for throttle inputs
2016-10-22 Fix brake code so that it is possible to set the brake ADC
2016-10-24 Add supply monitoring to start of code. Reset is 2.9v so CPU will only run when voltage is very close to the 3.3v target
2016-10-25 Fixed soft reset, begun adding code for GATT callbacks
2016-10-25 Added regen tapering to Coda controller code. You need it or you get a bucking bronco.
2016-10-25 Re-implement the "a" command on serial console that resets the BLE module
2016-10-25 Set CAR CAN speed to 250k for EVIC
    Change to config.h for EVIC
2016-10-26 The BLE code is now fully interrupt driven for everything - updates going both ways. Stability is still somewhat questionable but it works.
2016-10-27 Added back in CANIO code that was accidentally removed in some previous revision. It needed updating to the new SystemIO anyway.
2016-10-27 Changes because BLE library was renamed (to allow it to co-exist with official version on same machine)
2016-10-28 Tweaked watchdog timeout a little, removed extraneous function in BLE code, tweaked GATT update time a little.
2016-10-31 Switched to polling in interrupts for BLE
2016-10-31 Added a new component to collin.lbr library
2016-10-31 Fix 606 CAN query of IO states for both busses
    Added code to EVIC to attach filters for 606 incoming CAN messages so
    CANHANDLER can respond if they are received. We had no filter traps
    for the messages. Now works with either or both busses.
2016-11-02 Addition bug fixes and tweaks to BLE code.
2016-11-03 Add CAN0 and CAN1 speed to GATT characteristics for getting/setting.
2016-11-03 Print PACKHI, PACKLO, PACK, and CURRENT in L
    Added code in heartbeat.cpp to print out our pack voltage inputs and
    current sense
2016-11-03 Fix up code for pack low/high voltage measuring and shunt input
2016-11-03 Tapered Torque Commands in CODAMOTORCONTROLLER
    Attempted to incorporate the new taper commands for regen into
    CODAMOTORCONTROLLER.CPP to mirror use in DMOC645.
    These are motorcontroller configuration items for tapering torque below
    certain rpm values.
2016-11-03 Changed the scale for the offset value for pack low/high/current. Allows for a more precise offset.
2016-11-04 Added ability to calibrate pack voltage and current gain via giving it an externally measured value.
2016-11-04 Fix bugs in ADC calcs for pack high/low/current. Also change unity gain for them from 1024 to 16384 to give better readings.
2016-11-08 Much more implementation of BMS code, including a new device that uses the new pins on GEVCU6 to make it its own BMS.
2016-11-09 Additional implementation for BMS along with bug fixes in exsting code.
2017-01-22 Small tweaks to BLE code to make it work better
2017-01-24 Added code to CANHANDLER to printout CANIO messages
    Modification to print out loglevel2 messages showing 606 messages
    received over either CAN channel - used to test CAN capability in new
    hardware and set outputs per received 606 messages. Minor changes to
    CONFIG.H to make testing easier.
2017-01-24 GEVCU BMS OUTPUT
    Largely just set print statements in GEVCU BMS to WARN so that you can
    set loglevel to 2 and not get EVERYTHING that is happening in the GEVCU
    but just the BMS stuff.
2017-01-25 Get PACKLO to return as positive number
2017-01-25 Fix stupid errors in ADC calibration, tweaks to BMS code
2017-03-24 Add support for Rinehart Motion PM series inverters.
2017-07-06 Formatting changes to code, switch error messages to use error instead of debug logging.
2017-12-04 Bug fixes, updated Eagle library a bit.
2017-12-04 Fixed several issues with EEPROM initialization and saving
2018-05-18 Backlink to CADLAB.io has been added.
2019-01-22 Experimental changes to support UART over BLE for ELM327 emulation
2019-10-08 Add more parts to EagleCAD libraries
2019-10-08 Added some code to VehicleSpecific for a project of mine. It can serve as a real world example of how this module might look.
2019-10-08 Fixes in RMS code, remove EEPROM from Brusa as it breaks things
2019-10-09 Fixes to make the Brusa code not brick GEVCU. It's still hard coded though.
2020-10-21 Update README.md
    Update readme at long last to better specify libraries
2021-03-16 Add a new inverter (not done yet but hooked into the system), fix several compile time warnings, increment version number.
2021-06-27 More implementation of C300 controller code
2022-07-06 Documentation Added
2022-09-29 Fixes to C300 code to allow support for two different comm schemes, addition of code to support Ovar Charger/DCDC. Should also work fine with TCCH chargers.
2022-09-30 Added a new device that tracks gear position with a potentiometer
2022-12-05 update config file - project specific
2022-12-31 config update
2023-01-02 adding libs for redundancy
2023-01-11 update config -nominal voltage -forward creep -throt pot#
2023-02-27 remove grbl library
2023-03-16 removing
2023-03-16 "remove charge"
2023-03-16 "remove c300"
2023-03-16 remove power key
2023-03-16 remove evic
2023-03-16 remove ODB libs
2023-03-16 remove bms and charger
2023-03-16 remove unused motor controllers
2023-03-16 remove dcdc
2023-03-23 remove unused lib - microsmooth
2023-03-23 update libraries
2023-03-23 remove car bus - since we only have one can bus available
2023-03-23 remove unused lib imports
2023-03-23 refactor
2023-03-23 remove second bus
2023-03-23 migrate to mcp2515 library
2023-03-23 port to mcp2515 TODO port due timer
2023-03-23 refactor - move due time from lib to file and rename to evTimer
2023-03-23 remove FirmwareReceiver lib
2023-03-23 remove due timer
2023-03-23 remove serial console
2023-03-23 Removing everything down to the basics so it can run on 32k micro controller
2023-03-23 remove unused functions and fix imports
2023-03-23 remove heardbeat
2023-03-24 remove FD
2023-03-24 reduce logging
2023-04-11 Removed some old files that weren't updated in ages and no longer relevant
2023-04-11 Formatting changes to RMS motor driver code
2023-04-11 Addition of PWM and slow PWM to digital outputs. Slow PWM does PWM manually but allows for very slow PWM which is useful for things like pumps and Tesla heaters which want 5hz PWM.
2023-06-02 sending Can
2023-06-02 receiving
2023-06-05 sending and relays working
2023-06-05 fix last commit
2023-06-05 enable enable pib
2024-03-27 Add a PWM controlled heater device.
2024-03-27 Minor corrections to potgearselector and the Tesla battery manager
2024-03-27 Require BMS for RMS controller. Disable the controller if BMS is faulted.

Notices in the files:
parts and their libraries:
SparkFun-Passives: Licensing: CC v3.0 Share-Alike You are welcome to use this library for commercial purposes.
microbuilder: This work is placed in the public domain, and may be freely used for commercial and non-commercial work with the following conditions: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
